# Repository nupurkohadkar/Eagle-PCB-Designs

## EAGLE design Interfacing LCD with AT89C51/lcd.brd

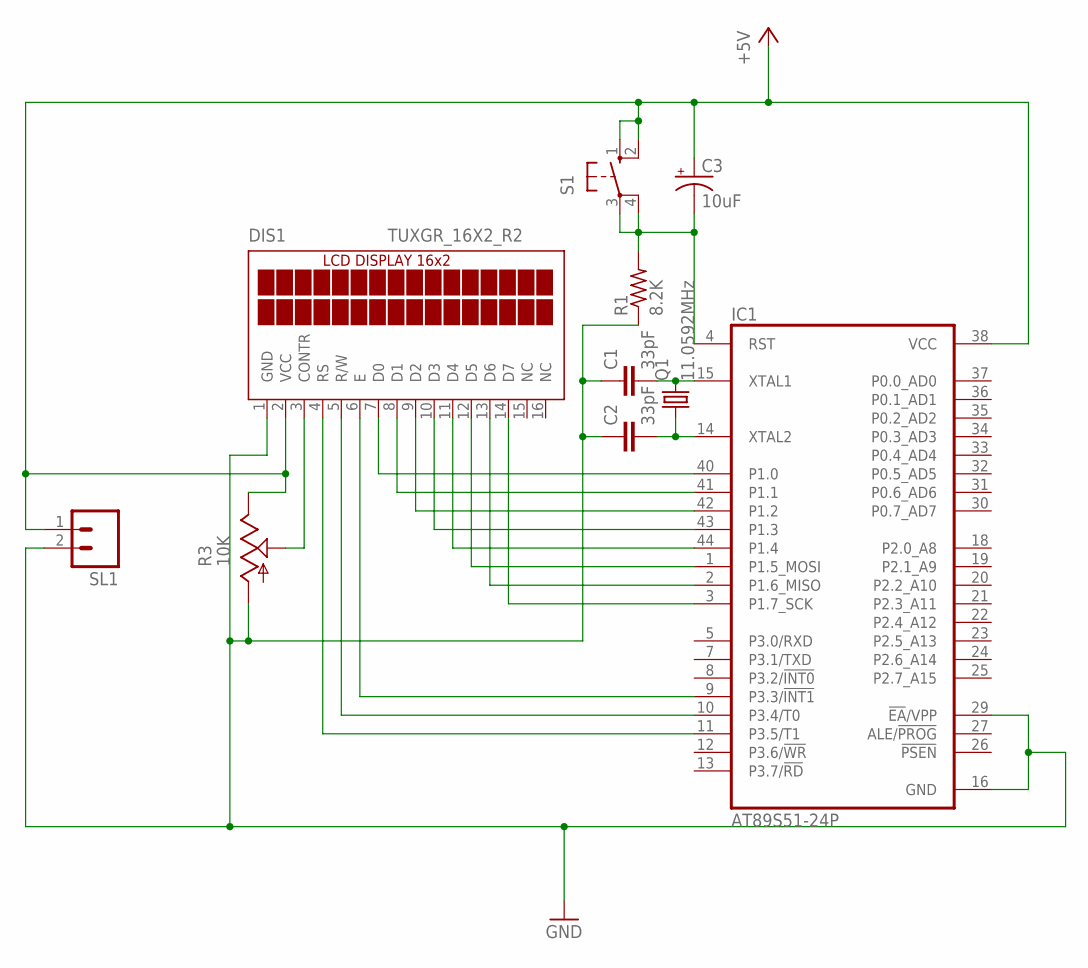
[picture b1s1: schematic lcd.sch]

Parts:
C1, C2: 33pF; C1206K
C3: 10uF; 140CLH-1010
DIS1: TUXGR_16X2_R2
IC1: AT89S51-24P; TQFP44
Q1: 11.0592MHz; TC26V
R1: 8.2K; M1206
R3: 10K; B25U
S1: 10-XX; B3F-10XX
SL1: MA02; 02PA

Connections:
+5V: C3.+, DIS1.2 (VCC), IC1.38 (VCC), R3.E, S1.1 (S), S1.2 (S1), SL1.1
GND: C1.1, C2.1, DIS1.1 (GND), IC1.16 (GND), IC1.17 (GND), IC1.29 (!EA!/VPP), R1.1, R3.A, SL1.2
unnamed: C1.2, IC1.15 (XTAL1), Q1.2
unnamed: C2.2, IC1.14 (XTAL2), Q1.1
unnamed: DIS1.5 (R/W), IC1.10 (P3.4/T0)
unnamed: DIS1.7 (D0), IC1.40 (P1.0)
unnamed: DIS1.6 (E), IC1.9 (P3.3/!INT1)
unnamed: DIS1.8 (D1), IC1.41 (P1.1)
unnamed: DIS1.9 (D2), IC1.42 (P1.2)
unnamed: DIS1.4 (RS), IC1.11 (P3.5/T1)
unnamed: DIS1.10 (D3), IC1.43 (P1.3)
unnamed: DIS1.11 (D4), IC1.44 (P1.4)
unnamed: DIS1.12 (D5), IC1.1 (P1.5_MOSI)
unnamed: DIS1.13 (D6), IC1.2 (P1.6_MISO)
unnamed: DIS1.14 (D7), IC1.3 (P1.7_SCK)
unnamed: DIS1.3 (CONTR), R3.S
unnamed: C3.-, IC1.4 (RST), R1.2, S1.3, S1.4 (P1)

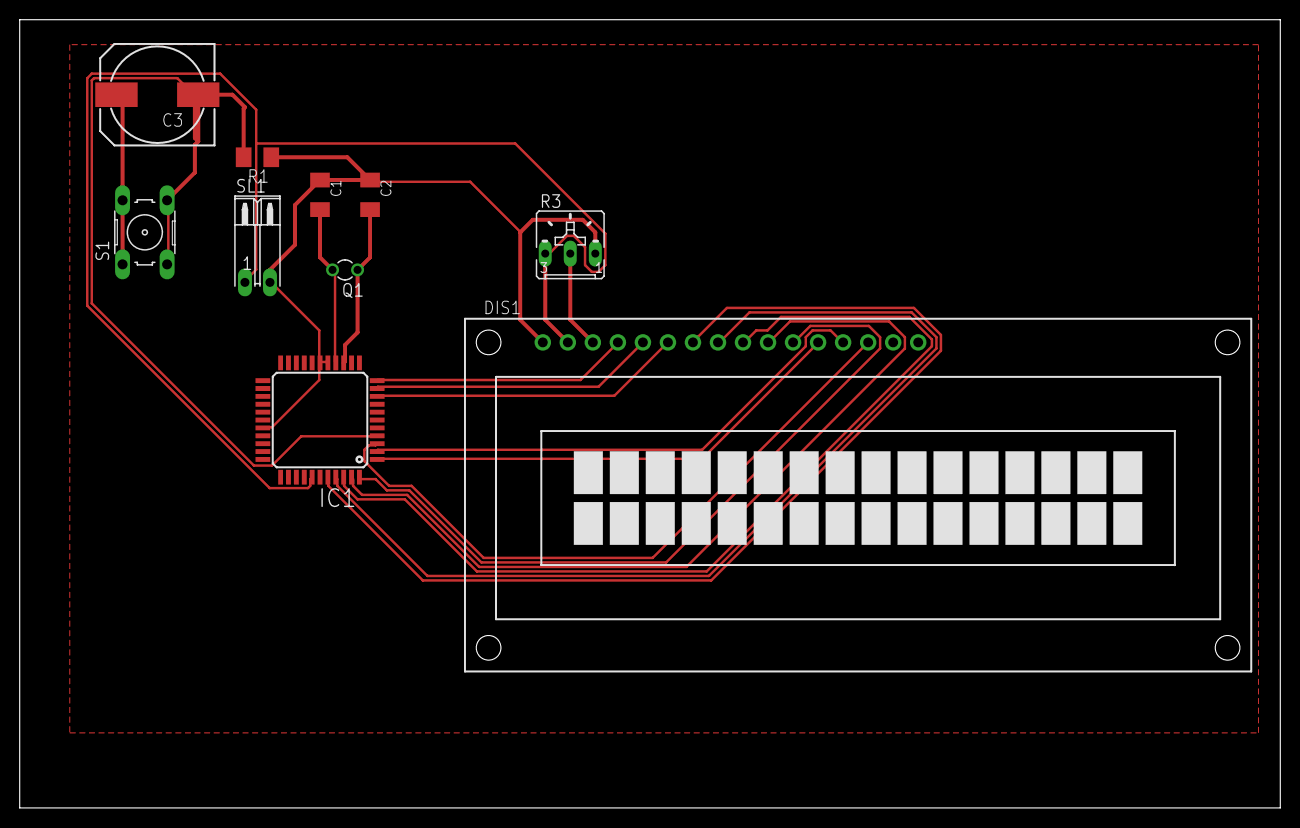
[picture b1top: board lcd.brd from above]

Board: 2 copper layers, 127.9 x 80.0 mm, 10 parts (0 on the bottom side), 17 nets.

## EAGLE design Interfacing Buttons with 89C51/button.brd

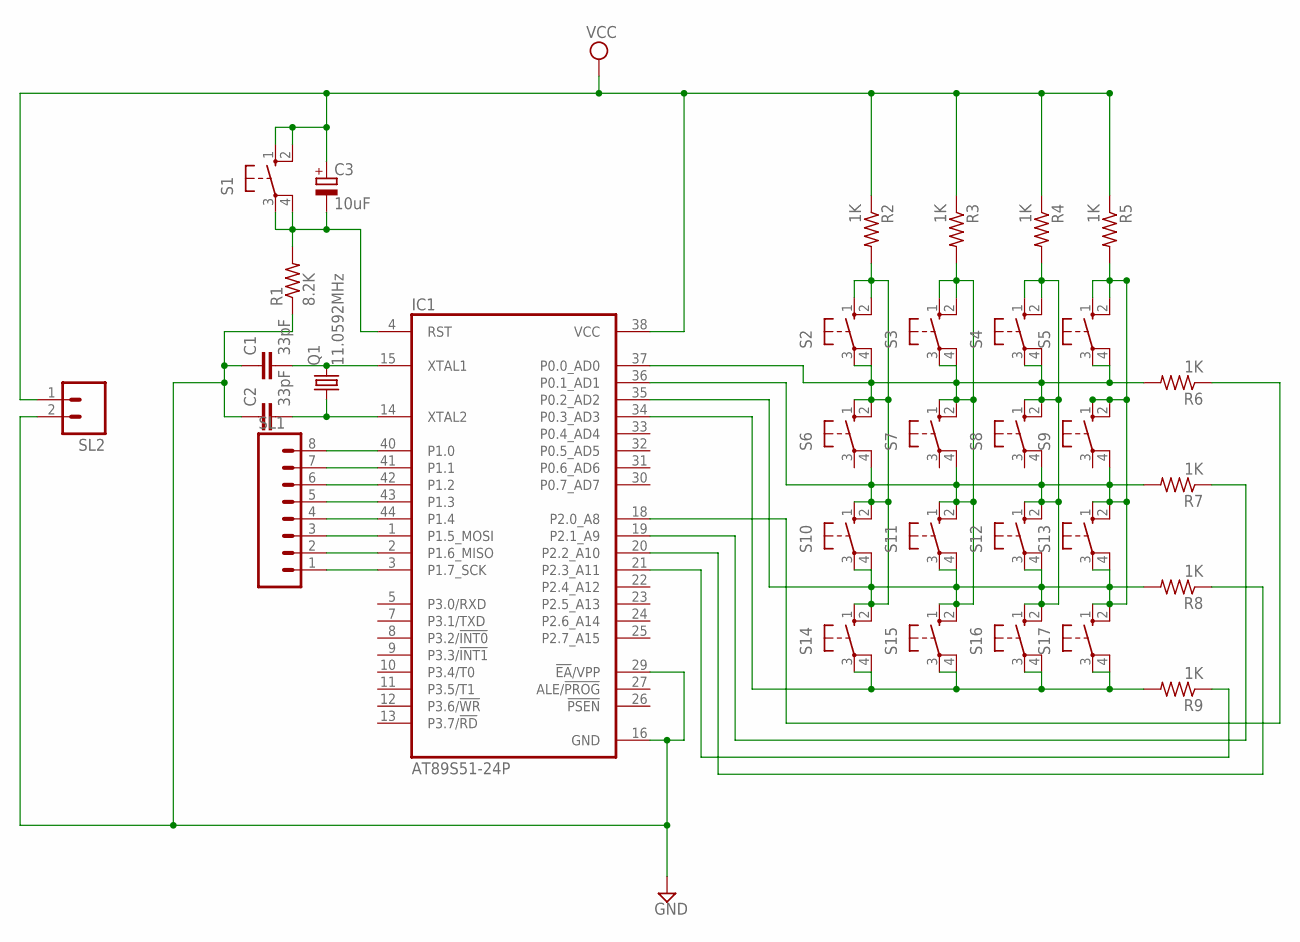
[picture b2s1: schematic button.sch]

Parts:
C1, C2: 33pF; C1206K
C3: 10uF; 140CLH-1010
IC1: AT89S51-24P; TQFP44
Q1: 11.0592MHz; TC26V
R1: 8.2K; R1206
R2, R3, R4, R5, R6, R7, R8, R9: 1K; M1206
S1, S2, S3, S4, S5, S6, S7, S8, S9, S10, S11, S12, S13, S14, S15, S16, S17: 10-XX; B3F-10XX
SL1: MA08; 08PA
SL2: MA02; 02PA

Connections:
GND: C1.1, C2.1, IC1.16 (GND), IC1.17 (GND), IC1.29 (!EA!/VPP), R1.1, SL2.2
unnamed: C1.2, IC1.15 (XTAL1), Q1.2
unnamed: C2.2, IC1.14 (XTAL2), Q1.1
unnamed: C3.-, IC1.4 (RST), R1.2, S1.3, S1.4 (P1)
unnamed: IC1.41 (P1.1), SL1.7
unnamed: IC1.42 (P1.2), SL1.6
unnamed: IC1.43 (P1.3), SL1.5
unnamed: IC1.40 (P1.0), SL1.8
unnamed: IC1.44 (P1.4), SL1.4
unnamed: IC1.1 (P1.5_MOSI), SL1.3
unnamed: IC1.2 (P1.6_MISO), SL1.2
unnamed: IC1.3 (P1.7_SCK), SL1.1
unnamed: IC1.21 (P2.3_A11), R9.1
unnamed: IC1.20 (P2.2_A10), R8.1
unnamed: IC1.19 (P2.1_A9), R7.1
unnamed: IC1.18 (P2.0_A8), R6.1
unnamed: IC1.35 (P0.2_AD2), IC1.36 (P0.1_AD1), IC1.37 (P0.0_AD0), R2.2, R3.2, R4.2, R5.2, R6.2, R7.2, R8.2, S2.1 (S), S2.2 (S1), S2.3, S2.4 (P1), S3.1 (S), S3.2 (S1), S3.3, S3.4 (P1), S4.1 (S), S4.2 (S1), S4.3, S4.4 (P1), S5.1 (S), S5.2 (S1), S5.3, S5.4 (P1), S6.1 (S), S6.2 (S1), S6.4 (P1), S7.1 (S), S7.2 (S1), S7.4 (P1), S8.1 (S), S8.2 (S1), S8.4 (P1), S9.1 (S), S9.2 (S1), S9.4 (P1), S10.1 (S), S10.2 (S1), S10.3, S10.4 (P1), S11.1 (S), S11.2 (S1), S11.3, S11.4 (P1), S12.1 (S), S12.2 (S1), S12.3, S12.4 (P1), S13.1 (S), S13.2 (S1), S13.3, S13.4 (P1), S14.1 (S), S14.2 (S1), S15.1 (S), S15.2 (S1), S16.1 (S), S16.2 (S1), S17.1 (S), S17.2 (S1)
unnamed: IC1.34 (P0.3_AD3), R9.2, S14.3, S14.4 (P1), S15.3, S15.4 (P1), S16.3, S16.4 (P1), S17.3, S17.4 (P1)
VCC: C3.+, IC1.38 (VCC), R2.1, R3.1, R4.1, R5.1, S1.1 (S), S1.2 (S1), SL2.1

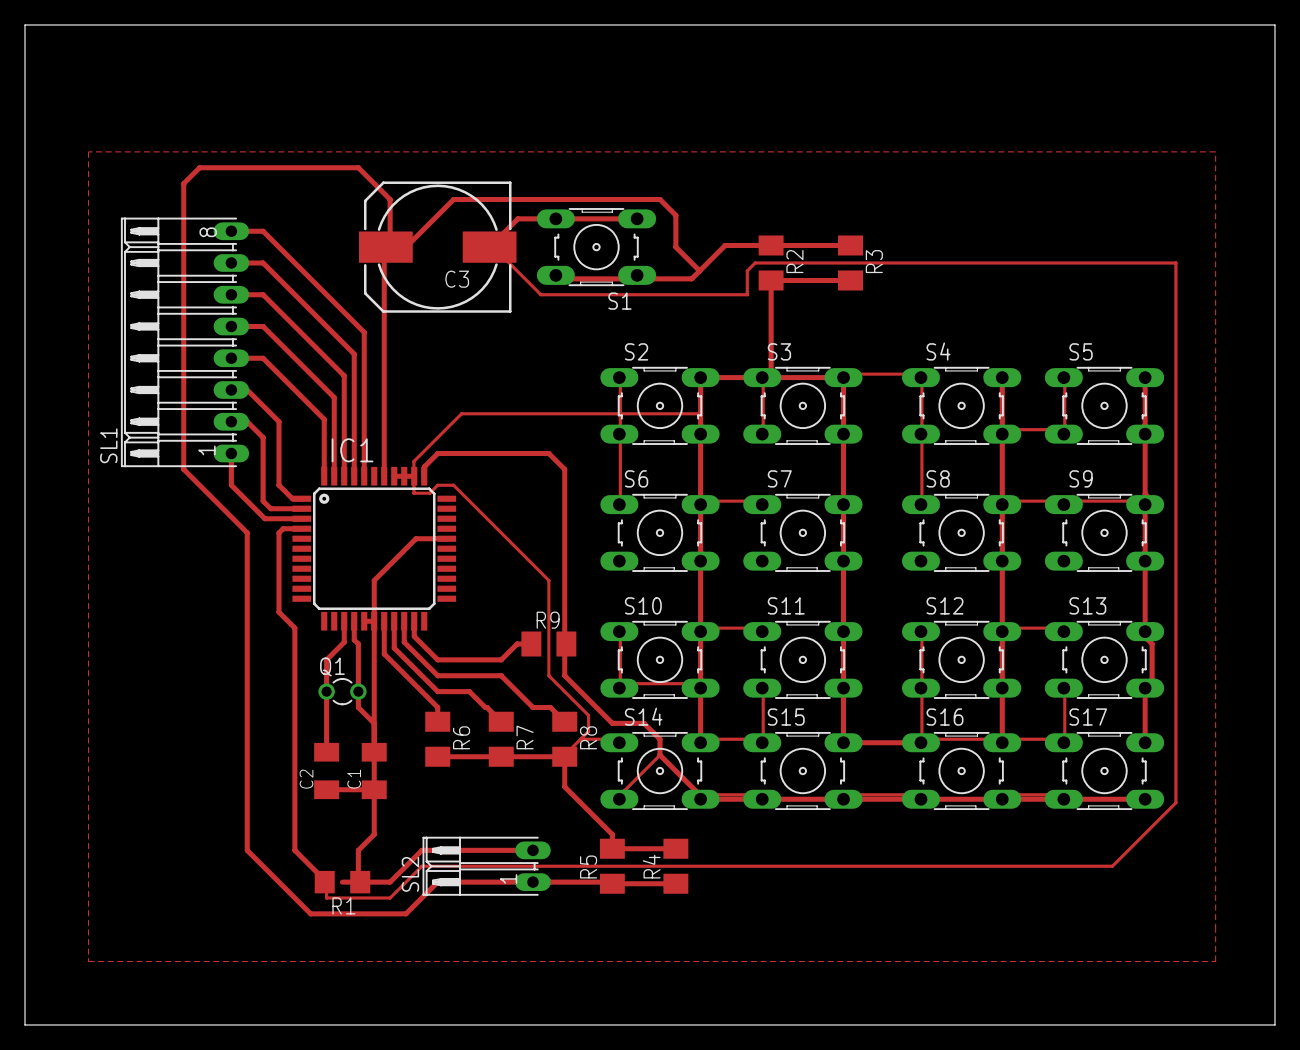
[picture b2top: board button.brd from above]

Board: 2 copper layers, 100.0 x 80.0 mm, 33 parts (0 on the bottom side), 19 nets.

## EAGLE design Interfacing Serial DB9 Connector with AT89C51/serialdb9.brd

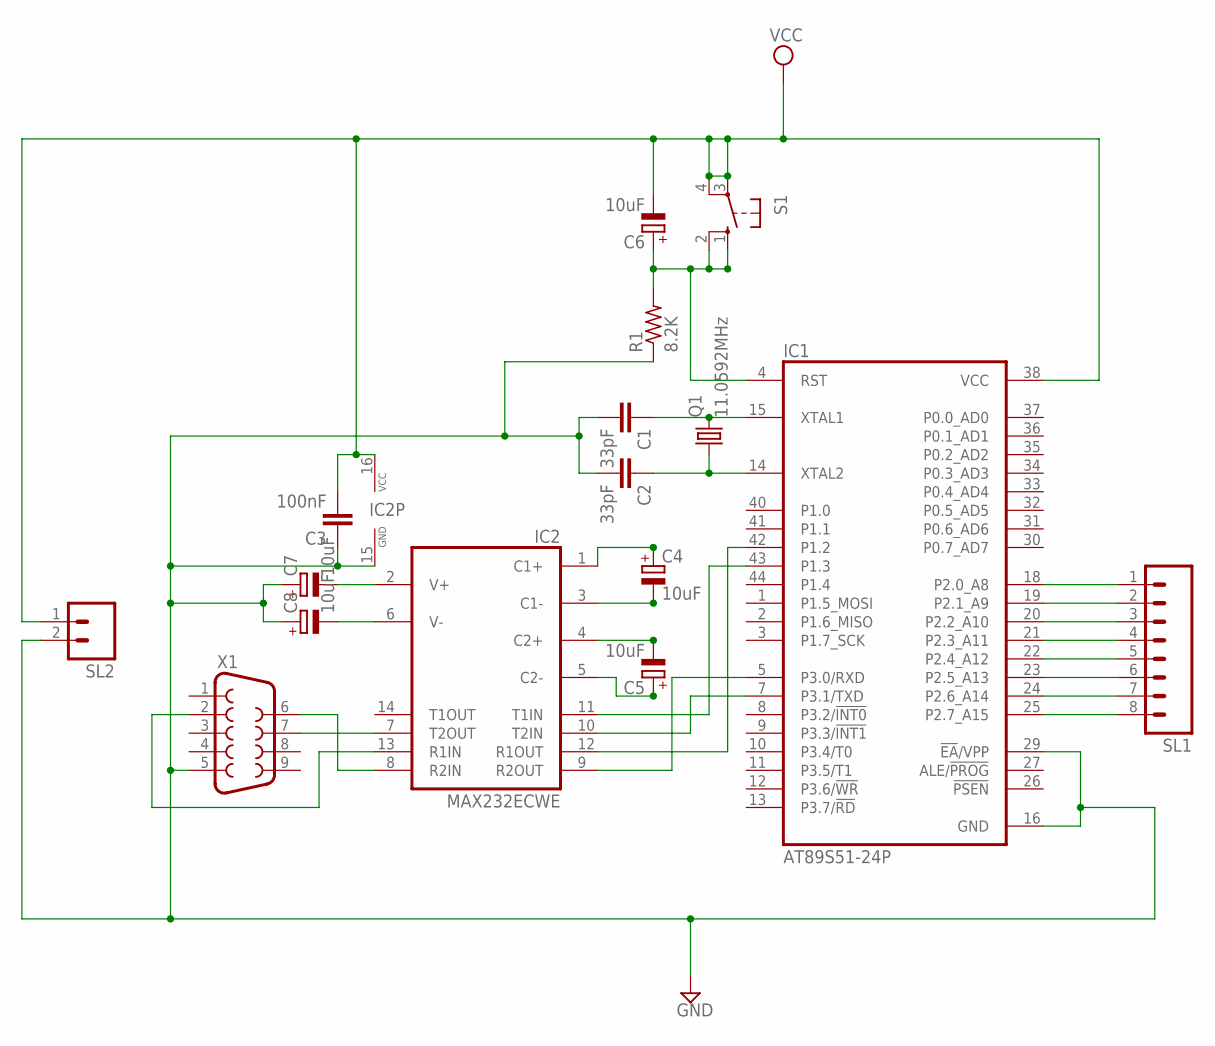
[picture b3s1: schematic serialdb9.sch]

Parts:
C1, C2: 33pF; C1206K
C3: 100nF; C1206K
C4, C5, C6, C7, C8: 10uF; 140CLH-1010
IC1: AT89S51-24P; TQFP44
IC2: MAX232ECWE; SO16L
Q1: 11.0592MHz; TC26V
R1: 8.2K; M1206
S1: 10-XX; B3F-10XX
SL1: MA08; 08PA
SL2: MA02; 02PA
X1: F09V

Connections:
GND: C1.2, C2.2, C3.1, C7.+, C8.+, IC1.16 (GND), IC1.17 (GND), IC1.29 (!EA!/VPP), IC2.15 (GND), R1.1, SL2.2, X1.5
unnamed: C4.-, IC2.3 (C1-)
unnamed: C4.+, IC2.1 (C1+)
unnamed: C5.-, IC2.4 (C2+)
unnamed: C5.+, IC2.5 (C2-)
unnamed: IC1.43 (P1.3), IC2.11 (T1IN)
unnamed: IC1.42 (P1.2), IC2.12 (R1OUT)
unnamed: IC1.7 (P3.1/TXD), IC2.10 (T2IN)
unnamed: IC1.5 (P3.0/RXD), IC2.9 (R2OUT)
unnamed: C6.+, IC1.4 (RST), R1.2, S1.1 (S), S1.2 (S1)
unnamed: C1.1, IC1.15 (XTAL1), Q1.2
unnamed: C2.1, IC1.14 (XTAL2), Q1.1
unnamed: IC1.25 (P2.7_A15), SL1.8
unnamed: IC1.24 (P2.6_A14), SL1.7
unnamed: IC1.23 (P2.5_A13), SL1.6
unnamed: IC1.22 (P2.4_A12), SL1.5
unnamed: IC1.21 (P2.3_A11), SL1.4
unnamed: IC1.20 (P2.2_A10), SL1.3
unnamed: IC1.19 (P2.1_A9), SL1.2
unnamed: IC1.18 (P2.0_A8), SL1.1
unnamed: IC2.7 (T2OUT), X1.7
unnamed: IC2.13 (R1IN), X1.2
unnamed: IC2.8 (R2IN), X1.6
unnamed: C7.-, IC2.2 (V+)
unnamed: C8.-, IC2.6 (V-)
VCC: C3.2, C6.-, IC1.38 (VCC), IC2.16 (VCC), S1.3, S1.4 (P1), SL2.1

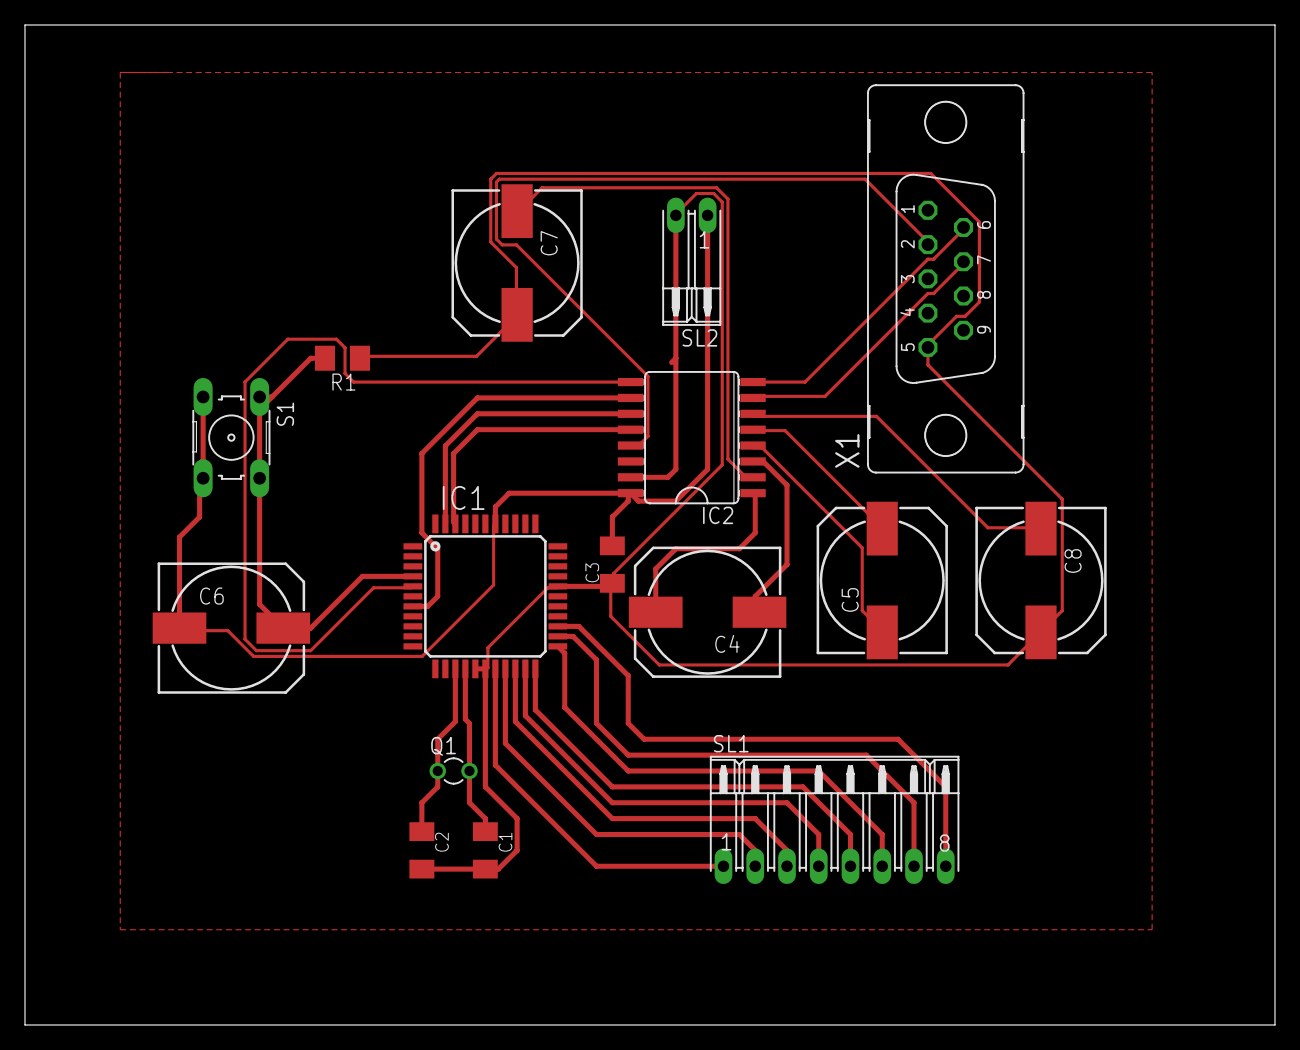
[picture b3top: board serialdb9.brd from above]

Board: 2 copper layers, 100.0 x 80.0 mm, 16 parts (0 on the bottom side), 26 nets.

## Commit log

2020-07-21 Adding some designs
